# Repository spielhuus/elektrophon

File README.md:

# **<font size="24">*elektrophon*</font>** 

**elektrophon** is a collection of modular synthesizer modules i have built. The module folders contain the schema and PCB files for kicad. You can find all the required files for changing the schemas and building gerber files in the projects.  

## **<font size="24">*ressources*</font>** 

ressources on the internet which provide information about electronic instruments.

* [Thomas Henry](http://birthofasynth.com/Thomas_Henry/TH_main.html) modules archived by [Scott Stites](http://birthofasynth.com/index.html). 
  * The [Electronic Music Circuits: The Reprints](https://web.archive.org/web/20190907204304/https://static.miraheze.org/sdiywiki/5/5d/The_Reprint_Collection_by_Thomas_Henry_CC_BY_NC.pdf) from Thomas Henry.
* [Synthesizer DIY pages of René Schmitz](https://www.schmitzbits.de/index.html)
* [Music from outer space](http://musicfromouterspace.com/)
* [yusynth: modular synth project](http://www.yusynth.net/Modular/index_en.html)
* [Ken Stones - CGS (Cat Girl Synth)](http://www.elby-designs.com/webtek/cgs/cgs.htm)
* [Osamu Hoshuyama - Unusual Synthesizer Circuits)](http://www5b.biglobe.ne.jp/~houshu/synth/)
* pdf collection of the [polyphony](http://www.muzines.co.uk/mags/pl/all) magazine
* free [electronotes](http://electronotes.netfirms.com/free.htm) newsletter published by Bernie Hutchins.

## **<font size="24">*featured software*</font>** 

list of some third party software used to develop the modules. for a complete list go to the arbeitsplatz article.

* [KiCad EDA](https://kicad.org/) A Cross Platform and Open Source Electronics Design Automation Suite.
* [ngspice](http://ngspice.sourceforge.net/index.html) is an open source spice simulator for electric and electronic circuits.
* [PySpice](https://pyspice.fabrice-salvaire.fr/releases/v1.4/overview.html) is an open source Python module which provides a Python interface to the Ngspice and Xyce circuit simulators.
* [Jupyter](https://jupyter.org/) interactive Python notebook.  
* [SchemDraw](https://schemdraw.readthedocs.io/en/latest/index.html)  is a Python package for producing electrical circuit schematic diagrams.

---

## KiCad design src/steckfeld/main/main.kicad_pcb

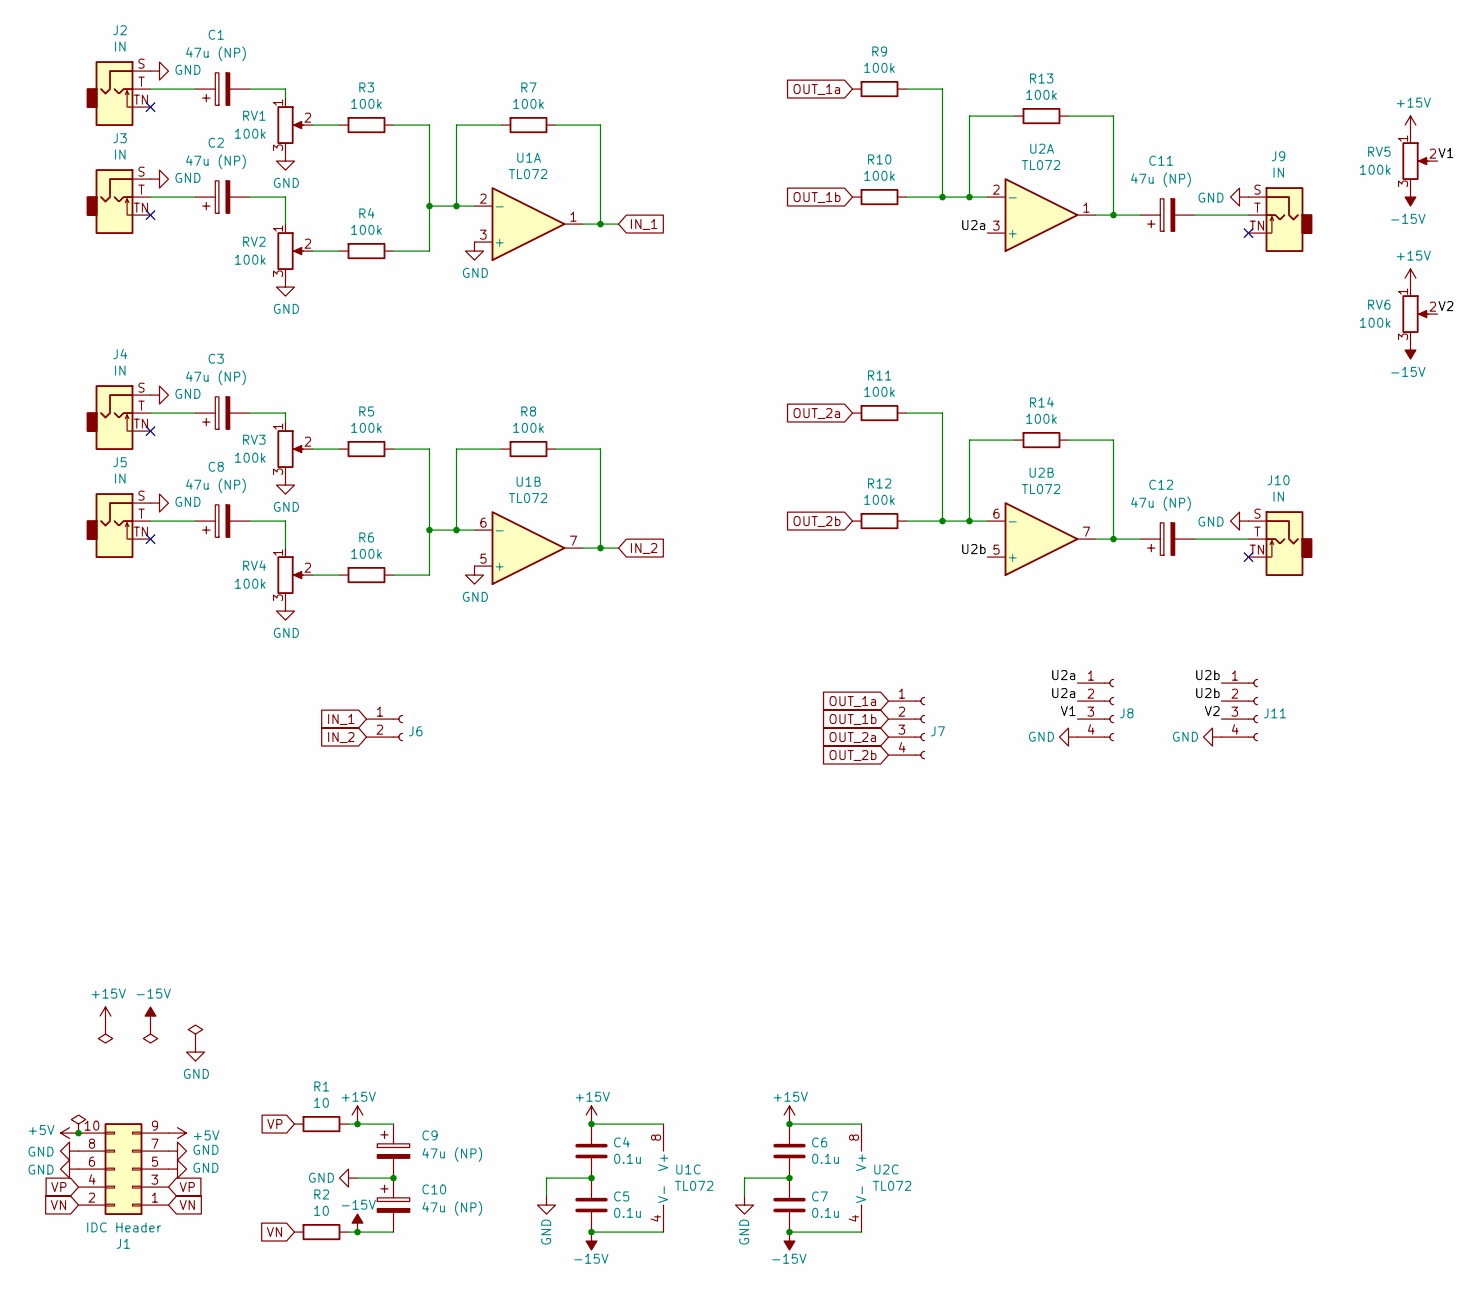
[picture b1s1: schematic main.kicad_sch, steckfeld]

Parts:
C1, C2, C3, C8, C11, C12: 47u (NP); PinSocket_1x02_P2.54mm_Vertical
C4, C5, C6, C7: 0.1u; C_Disc_D3.4mm_W2.1mm_P2.50mm
C9, C10: 47u (NP); CP_Radial_D5.0mm_P2.00mm
J1: IDC Header; IDC-Header_2x05_P2.54mm_Vertical
J2, J3, J4, J5, J9, J10: IN; Jack_3.5mm_WQP-PJ398SM_Vertical
J6: Conn_01x02_Female; PinSocket_1x02_P2.54mm_Vertical
J7, J8, J11: Conn_01x04_Female; PinSocket_1x04_P2.54mm_Vertical
R1, R2: 10; R_Axial_DIN0204_L3.6mm_D1.6mm_P2.54mm_Vertical
R3, R4, R5, R6, R7, R8, R9, R10, R11, R12, R13, R14: 100k; PinSocket_1x02_P2.54mm_Vertical
RV1, RV2, RV3, RV4, RV5, RV6: 100k; Potentiometer_Bourns_PTV09A-1_Single_Vertical
U1, U2: TL072; DIP-8_W7.62mm_Socket

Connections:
+5V: J1.9, J1.10
+15V: C4.1, C6.1, C9.1, R1.1, RV5.1, RV6.1, U1.8 (V+), U2.8 (V+)
-15V: C5.2, C7.2, C10.2, R2.1, RV5.3, RV6.3, U1.4 (V-), U2.4 (V-)
/U2a: J8.1, J8.2, U2.3 (+)
/U2b: J11.1, J11.2, U2.5 (+)
/V1: J8.3, RV5.2
/V2: J11.3, RV6.2
GND: C4.2, C5.1, C6.2, C7.1, C9.2, C10.1, J1.5, J1.6, J1.7, J1.8, J2.S, J3.S, J4.S, J5.S, J8.4, J9.S, J10.S, J11.4, RV1.3, RV2.3, RV3.3, RV4.3, U1.3 (+), U1.5 (+)
IN_1: J6.1, R7.1, U1.1
IN_2: J6.2, R8.1, U1.7
unnamed: C1.1, J2.T
unnamed: C1.2, RV1.1
unnamed: C2.1, J3.T
unnamed: C2.2, RV2.1
unnamed: C3.1, J4.T
unnamed: C3.2, RV3.1
unnamed: C8.1, J5.T
unnamed: C8.2, RV4.1
unnamed: C11.1, R13.1, U2.1
unnamed: C11.2, J9.T
unnamed: C12.1, R14.1, U2.7
unnamed: C12.2, J10.T
unnamed: R3.1, R4.1, R7.2, U1.2 (-)
unnamed: R3.2, RV1.2
unnamed: R4.2, RV2.2
unnamed: R5.1, R6.1, R8.2, U1.6 (-)
unnamed: R5.2, RV3.2
unnamed: R6.2, RV4.2
unnamed: R9.1, R10.1, R13.2, U2.2 (-)
unnamed: R11.1, R12.1, R14.2, U2.6 (-)
OUT_1a: J7.1, R9.2
OUT_1b: J7.2, R10.2
OUT_2a: J7.3, R11.2
OUT_2b: J7.4, R12.2
VN: J1.1, J1.2, R2.2
VP: J1.3, J1.4, R1.2

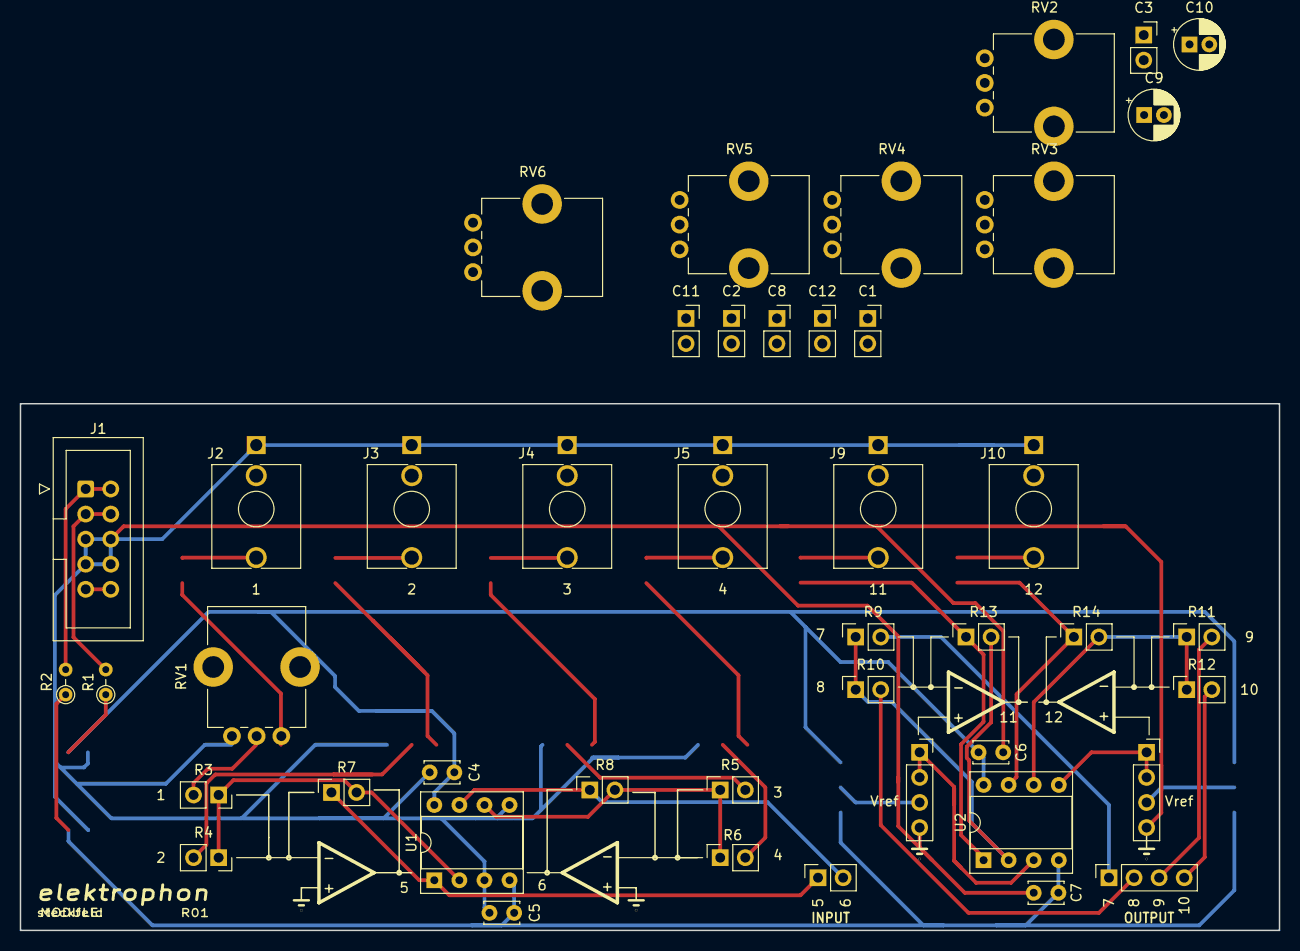
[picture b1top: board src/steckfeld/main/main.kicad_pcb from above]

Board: 2 copper layers, 127.5 x 53.3 mm, 45 parts (0 on the bottom side), 36 nets.

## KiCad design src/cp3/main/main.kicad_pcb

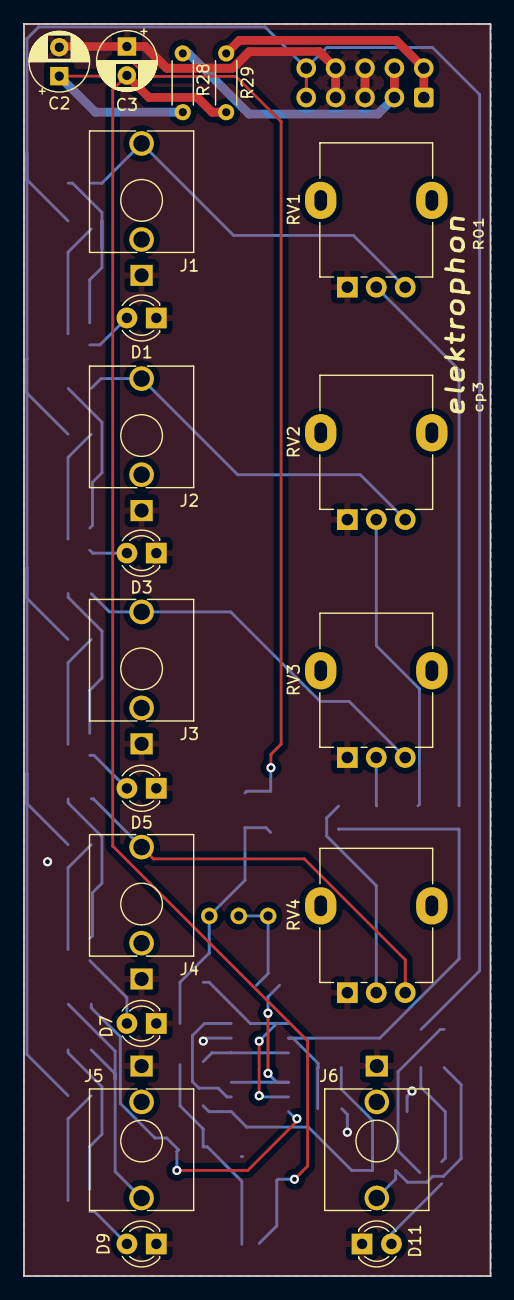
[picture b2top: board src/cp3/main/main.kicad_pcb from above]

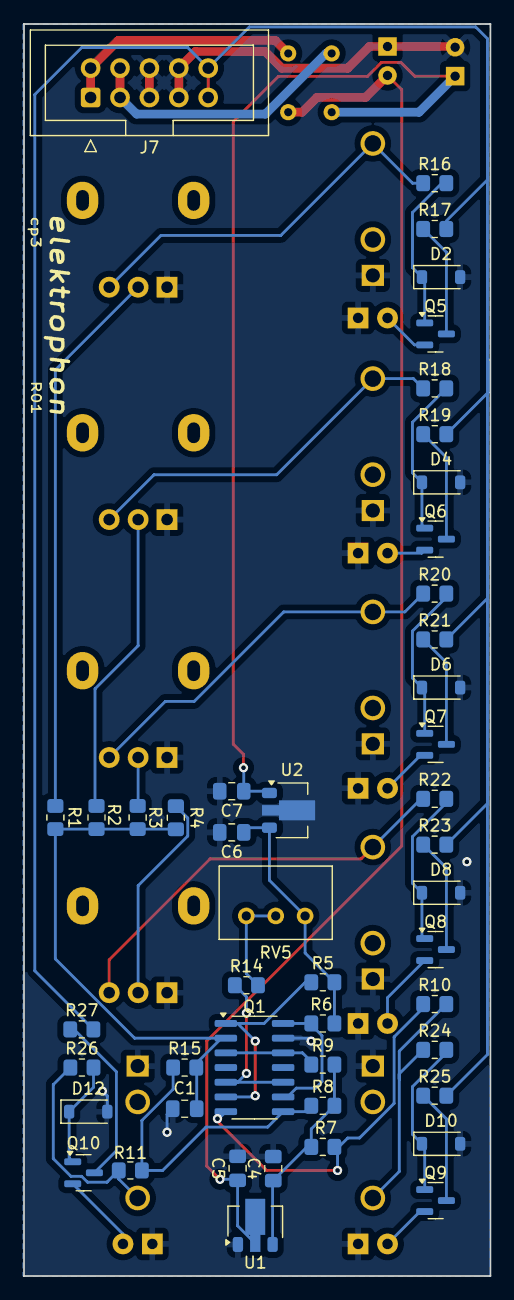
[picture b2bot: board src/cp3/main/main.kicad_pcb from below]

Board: 2 copper layers, 40.3 x 108.2 mm, 67 parts (47 on the bottom side), 44 nets.

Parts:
C1: 3.3n; C_0805_2012Metric_Pad1.18x1.45mm_HandSolder
C2, C3: 10u; CP_Radial_D5.0mm_P2.50mm
C4, C6: 0.33u; C_0805_2012Metric_Pad1.18x1.45mm_HandSolder
C5: 1.0u; C_0805_2012Metric_Pad1.18x1.45mm_HandSolder
C7: 0.01; C_0805_2012Metric_Pad1.18x1.45mm_HandSolder
D1, D3, D5, D7: LED (Green); LED_D3.0mm
D2, D4, D6, D8, D10, D12: 1N4148W; D_SOD-123
D9, D11: LED (Red); LED_D3.0mm
J1, J2, J3, J4, J5, J6: PJ398SM; Jack_3.5mm_WQP-PJ398SM_Vertical
J7: IDC_Header; IDC-Header_2x05_P2.54mm_Vertical
Q1: THAT340; SOIC-14_3.9x8.7mm_P1.27mm
Q5, Q6, Q7, Q8, Q9, Q10: MMBT3904; SOT-23
R1, R2, R3, R4: 22k; R_0805_2012Metric_Pad1.20x1.40mm_HandSolder
R5, R6: 15k; R_0805_2012Metric_Pad1.20x1.40mm_HandSolder
R7, R8: 560; R_0805_2012Metric_Pad1.20x1.40mm_HandSolder
R9: 6.8k; R_0805_2012Metric_Pad1.20x1.40mm_HandSolder
R10, R11: 100; R_0805_2012Metric_Pad1.20x1.40mm_HandSolder
R14: 200; R_0805_2012Metric_Pad1.20x1.40mm_HandSolder
R15: 47k; R_0805_2012Metric_Pad1.20x1.40mm_HandSolder
R16, R18, R20, R22, R24, R26: 100k; R_0805_2012Metric_Pad1.20x1.40mm_HandSolder
R17, R19, R21, R23, R25, R27: 5.1k; R_0805_2012Metric_Pad1.20x1.40mm_HandSolder
R28, R29: 10; R_Axial_DIN0204_L3.6mm_D1.6mm_P5.08mm_Horizontal
RV1, RV2, RV3, RV4: 50k (A); Potentiometer_Alpha_RD901F-40-00D_Single_Vertical
RV5: 100; Potentiometer_Bourns_3299W_Vertical
U1: NJM79L06; SOT-89-3
U2: uA7812; SOT-89-3

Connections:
+5V: J7.9, J7.10, R17.2, R19.2, R21.2, R23.2, R25.2, R27.2
+12V: C6.1, R5.2, R6.1, RV5.3, U2.3 (OUT)
+15V: C2.1, C7.1, R28.2, U2.1 (IN)
-6V: C4.1, R7.2, R8.2, R9.2, U1.3 (VO)
-15V: C3.2, C5.1, R29.1, U1.2 (VI)
/IN_1: R1.1, RV1.2
/IN_2: R2.2, RV2.2
/IN_3: R3.2, RV3.2
/IN_4: R4.2, RV4.2
/IN_a: J1.T, R16.1, RV1.3
/IN_b: J2.T, R18.1, RV2.3
/IN_c: J3.T, R20.1, RV3.3
/IN_d: J4.T, R22.1, RV4.3
/OUT_A: J5.T, R10.2, R24.1
/OUT_B: J6.T, R11.2, R26.1
/VN: J7.1, J7.2, R29.2
/VP: J7.3, J7.4, R28.1
GND: C1.2, C2.2, C3.1, C4.2, C5.2, C6.2, C7.2, D1.1 (K), D2.2 (A), D3.1 (K), D4.2 (A), D5.1 (K), D6.2 (A), D7.1 (K), D8.2 (A), D9.1 (K), D10.2 (A), D11.1 (K), D12.2 (A), J1.S, J2.S, J3.S, J4.S, J5.S, J6.S, J7.5, J7.6, J7.7, J7.8, Q1.13 (B), RV1.1, RV2.1, RV3.1, RV4.1, U1.1 (GND), U2.2 (GND)
unnamed: D1.2 (A), Q5.2 (E)
unnamed: D2.1 (K), Q5.1 (B), R16.2
unnamed: D3.2 (A), Q6.2 (E)
unnamed: D4.1 (K), Q6.1 (B), R18.2
unnamed: D5.2 (A), Q7.2 (E)
unnamed: D6.1 (K), Q7.1 (B), R20.2
unnamed: D7.2 (A), Q8.2 (E)
unnamed: D8.1 (K), Q8.1 (B), R22.2
unnamed: D9.2 (A), Q9.2 (E)
unnamed: D10.1 (K), Q9.1 (B), R24.2
unnamed: D11.2 (A), Q10.2 (E)
unnamed: D12.1 (K), Q10.1 (B), R26.2
unnamed: C1.1, Q1.2 (B), R1.2, R2.1, R3.1, R4.1, R15.2
unnamed: Q1.1 (C), Q1.6 (B), R5.1
unnamed: Q1.3 (E), Q1.12 (E), R9.1
unnamed: Q1.9 (B), Q1.14 (C), R6.2
unnamed: Q1.5 (C), Q1.10, R14.1
unnamed: Q1.7 (E), R7.1, R10.1
unnamed: Q1.8 (E), R8.1, R11.1, R15.1
unnamed: Q5.3 (C), R17.1
unnamed: Q6.3 (C), R19.1
unnamed: Q7.3 (C), R21.1
unnamed: Q8.3 (C), R23.1
unnamed: Q9.3 (C), R25.1
unnamed: Q10.3 (C), R27.1
unnamed: R14.2, RV5.1, RV5.2

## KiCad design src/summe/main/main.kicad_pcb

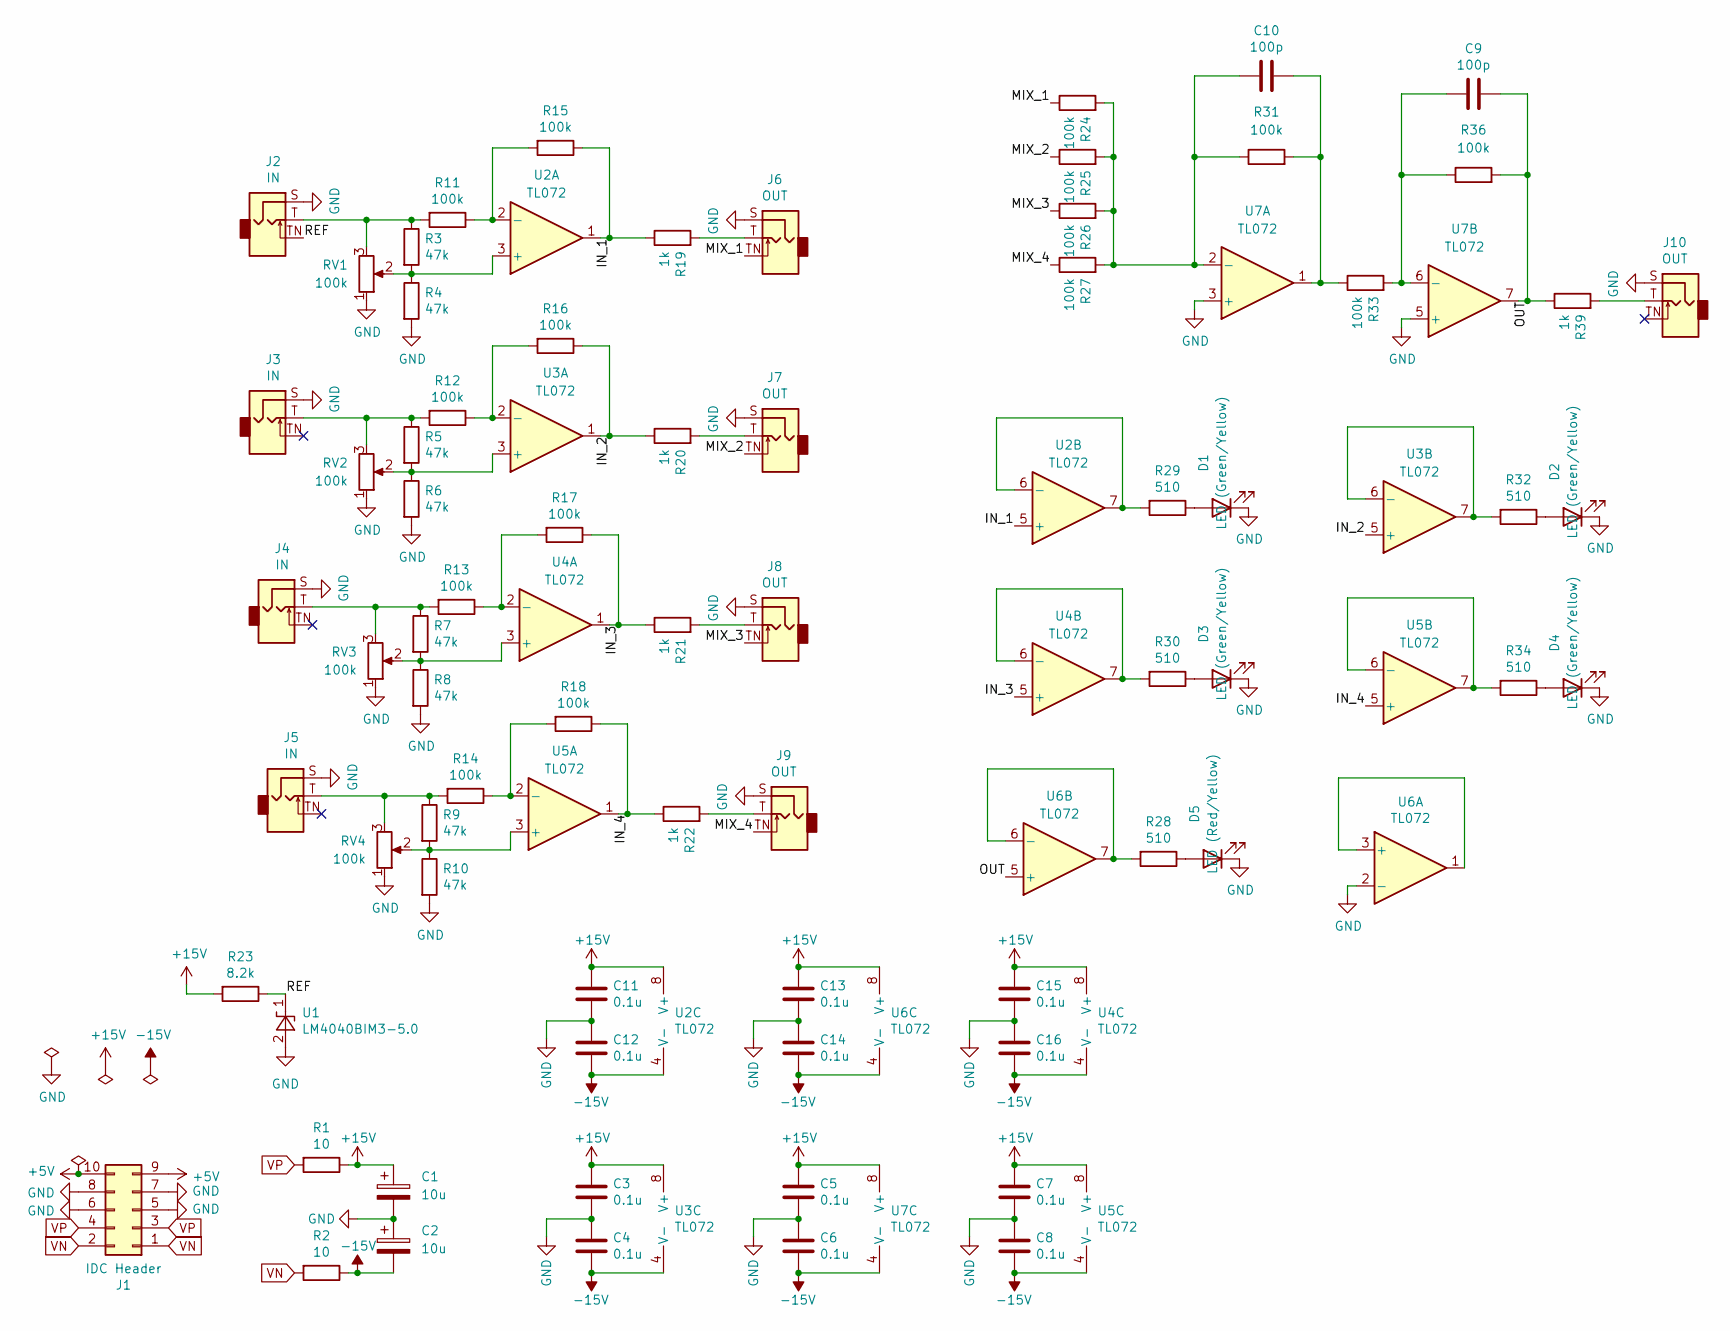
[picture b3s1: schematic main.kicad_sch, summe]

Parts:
C1, C2: 10u; CP_Radial_D5.0mm_P2.50mm
C3, C4, C5, C6, C7, C8, C11, C12, C13, C14, C15, C16: 0.1u; C_0805_2012Metric_Pad1.18x1.45mm_HandSolder
C9, C10: 100p; C_0805_2012Metric_Pad1.18x1.45mm_HandSolder
D1, D2, D3, D4: LED (Green/Yellow); LED_D3.0mm
D5: LED (Red/Yellow); LED_D3.0mm
J1: IDC Header; IDC-Header_2x05_P2.54mm_Vertical
J2, J3, J4, J5: IN; Jack_3.5mm_WQP-PJ398SM_Vertical
J6, J7, J8, J9, J10: OUT; Jack_3.5mm_WQP-PJ398SM_Vertical
R1, R2: 10; R_Axial_DIN0204_L3.6mm_D1.6mm_P2.54mm_Vertical
R3, R4, R5, R6, R7, R8, R9, R10: 47k; R_0805_2012Metric_Pad1.20x1.40mm_HandSolder
R11, R12, R13, R14, R15, R16, R17, R18, R24, R25, R26, R27, R31, R33, R36: 100k; R_0805_2012Metric_Pad1.20x1.40mm_HandSolder
R19, R20, R21, R22, R39: 1k; R_0805_2012Metric_Pad1.20x1.40mm_HandSolder
R23: 8.2k; R_0805_2012Metric_Pad1.20x1.40mm_HandSolder
R28, R29, R30, R32, R34: 510; R_0805_2012Metric_Pad1.20x1.40mm_HandSolder
RV1, RV2, RV3, RV4: 100k; Potentiometer_Alpha_RD901F-40-00D_Single_Vertical
U1: LM4040BIM3-5.0; SOT-23
U2, U3, U4, U5, U6, U7: TL072; SOIC-8_3.9x4.9mm_P1.27mm

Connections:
+5V: J1.9, J1.10
+15V: C1.1, C3.1, C5.1, C7.1, C11.1, C13.1, C15.1, R1.1, R23.2, U2.8 (V+), U3.8 (V+), U4.8 (V+), U5.8 (V+), U6.8 (V+), U7.8 (V+)
-15V: C2.2, C4.2, C6.2, C8.2, C12.2, C14.2, C16.2, R2.1, U2.4 (V-), U3.4 (V-), U4.4 (V-), U5.4 (V-), U6.4 (V-), U7.4 (V-)
/IN_1: R15.1, R19.1, U2.1, U2.5 (+)
/IN_2: R16.1, R20.1, U3.1, U3.5 (+)
/IN_3: R17.1, R21.1, U4.1, U4.5 (+)
/IN_4: R18.1, R22.1, U5.1, U5.5 (+)
/MIX_1: J6.TN, R24.1
/MIX_2: J7.TN, R25.1
/MIX_3: J8.TN, R26.1
/MIX_4: J9.TN, R27.1
/OUT: C9.1, R36.2, R39.1, U6.5 (+), U7.7
/REF: J2.TN, R23.1, U1.1 (K)
GND: C1.2, C2.1, C3.2, C4.1, C5.2, C6.1, C7.2, C8.1, C11.2, C12.1, C13.2, C14.1, C15.2, C16.1, D1.1 (K), D2.1 (K), D3.1 (K), D4.1 (K), D5.1 (K), J1.5, J1.6, J1.7, J1.8, J2.S, J3.S, J4.S, J5.S, J6.S, J7.S, J8.S, J9.S, J10.S, R4.2, R6.2, R8.2, R10.2, RV1.1, RV2.1, RV3.1, RV4.1, U1.2 (A), U6.2 (-), U7.3 (+), U7.5 (+)
unnamed: C10.1, R31.2, R33.1, U7.1
unnamed: D1.2 (A), R29.1
unnamed: D2.2 (A), R32.1
unnamed: D3.2 (A), R30.1
unnamed: D4.2 (A), R34.1
unnamed: D5.2 (A), R28.1
unnamed: J2.T, R3.1, R11.2, RV1.3
unnamed: J3.T, R5.1, R12.2, RV2.3
unnamed: J4.T, R7.1, R13.2, RV3.3
unnamed: J5.T, R9.1, R14.2, RV4.3
unnamed: J6.T, R19.2
unnamed: J7.T, R20.2
unnamed: J8.T, R21.2
unnamed: J9.T, R22.2
unnamed: J10.T, R39.2
unnamed: R3.2, R4.1, RV1.2, U2.3 (+)
unnamed: R11.1, R15.2, U2.2 (-)
unnamed: R29.2, U2.6 (-), U2.7
unnamed: R5.2, R6.1, RV2.2, U3.3 (+)
unnamed: R12.1, R16.2, U3.2 (-)
unnamed: R32.2, U3.6 (-), U3.7
unnamed: R7.2, R8.1, RV3.2, U4.3 (+)
unnamed: R13.1, R17.2, U4.2 (-)
unnamed: R30.2, U4.6 (-), U4.7
unnamed: R9.2, R10.1, RV4.2, U5.3 (+)
unnamed: R14.1, R18.2, U5.2 (-)
unnamed: R34.2, U5.6 (-), U5.7
unnamed: U6.1, U6.3 (+)
unnamed: R28.2, U6.6 (-), U6.7
unnamed: C10.2, R24.2, R25.2, R26.2, R27.2, R31.1, U7.2 (-)
unnamed: C9.2, R33.2, R36.1, U7.6 (-)
VN: J1.1, J1.2, R2.2
VP: J1.3, J1.4, R1.2

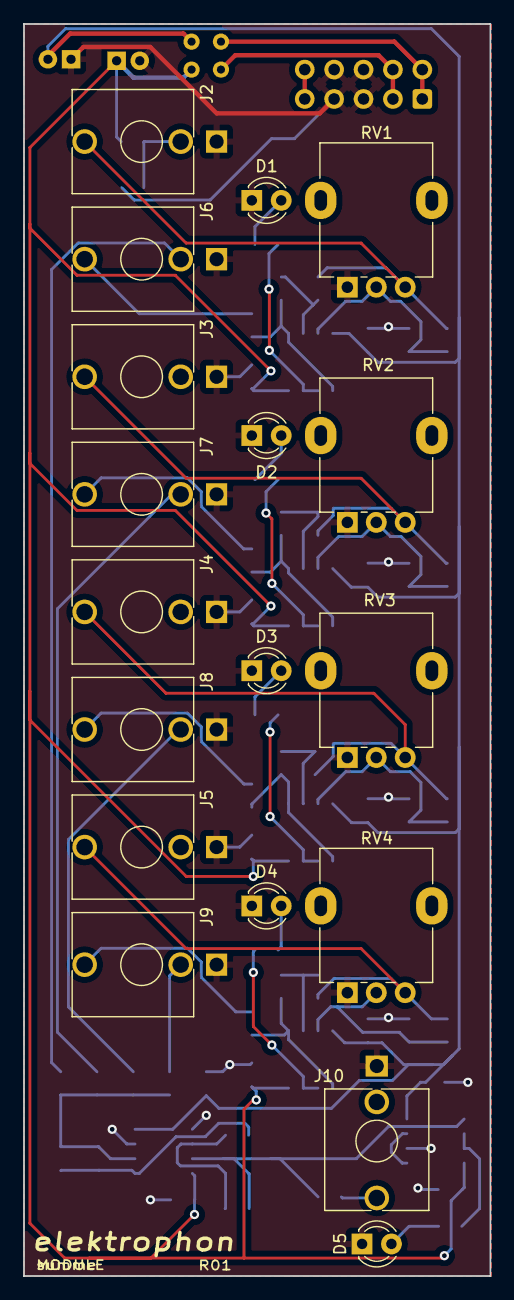
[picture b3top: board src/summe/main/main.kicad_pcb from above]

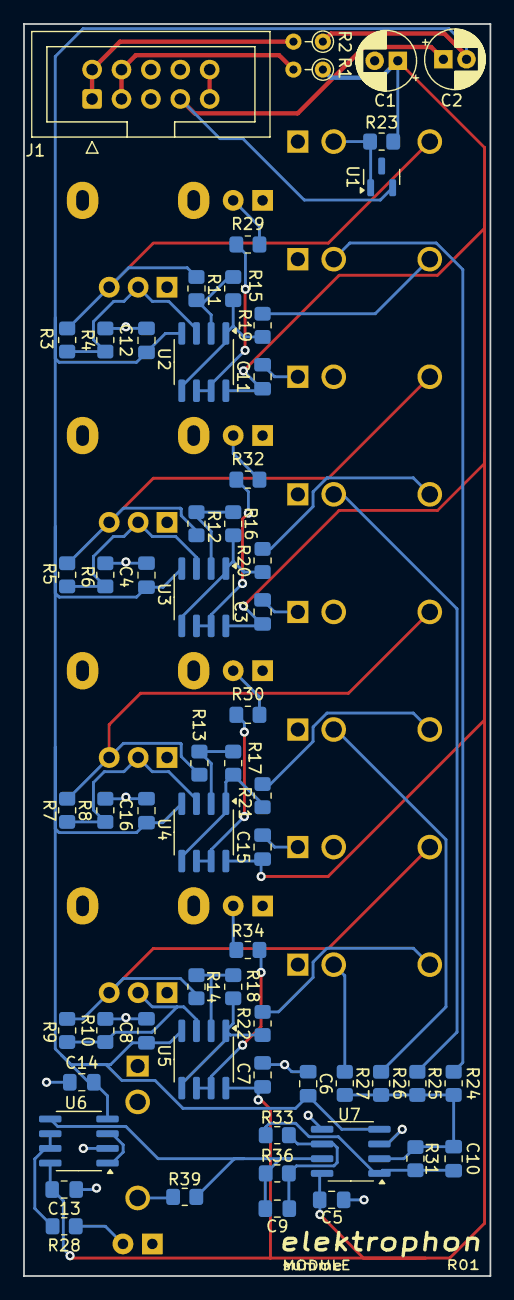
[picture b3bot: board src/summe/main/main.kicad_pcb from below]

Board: 2 copper layers, 40.3 x 108.2 mm, 78 parts (60 on the bottom side), 47 nets.

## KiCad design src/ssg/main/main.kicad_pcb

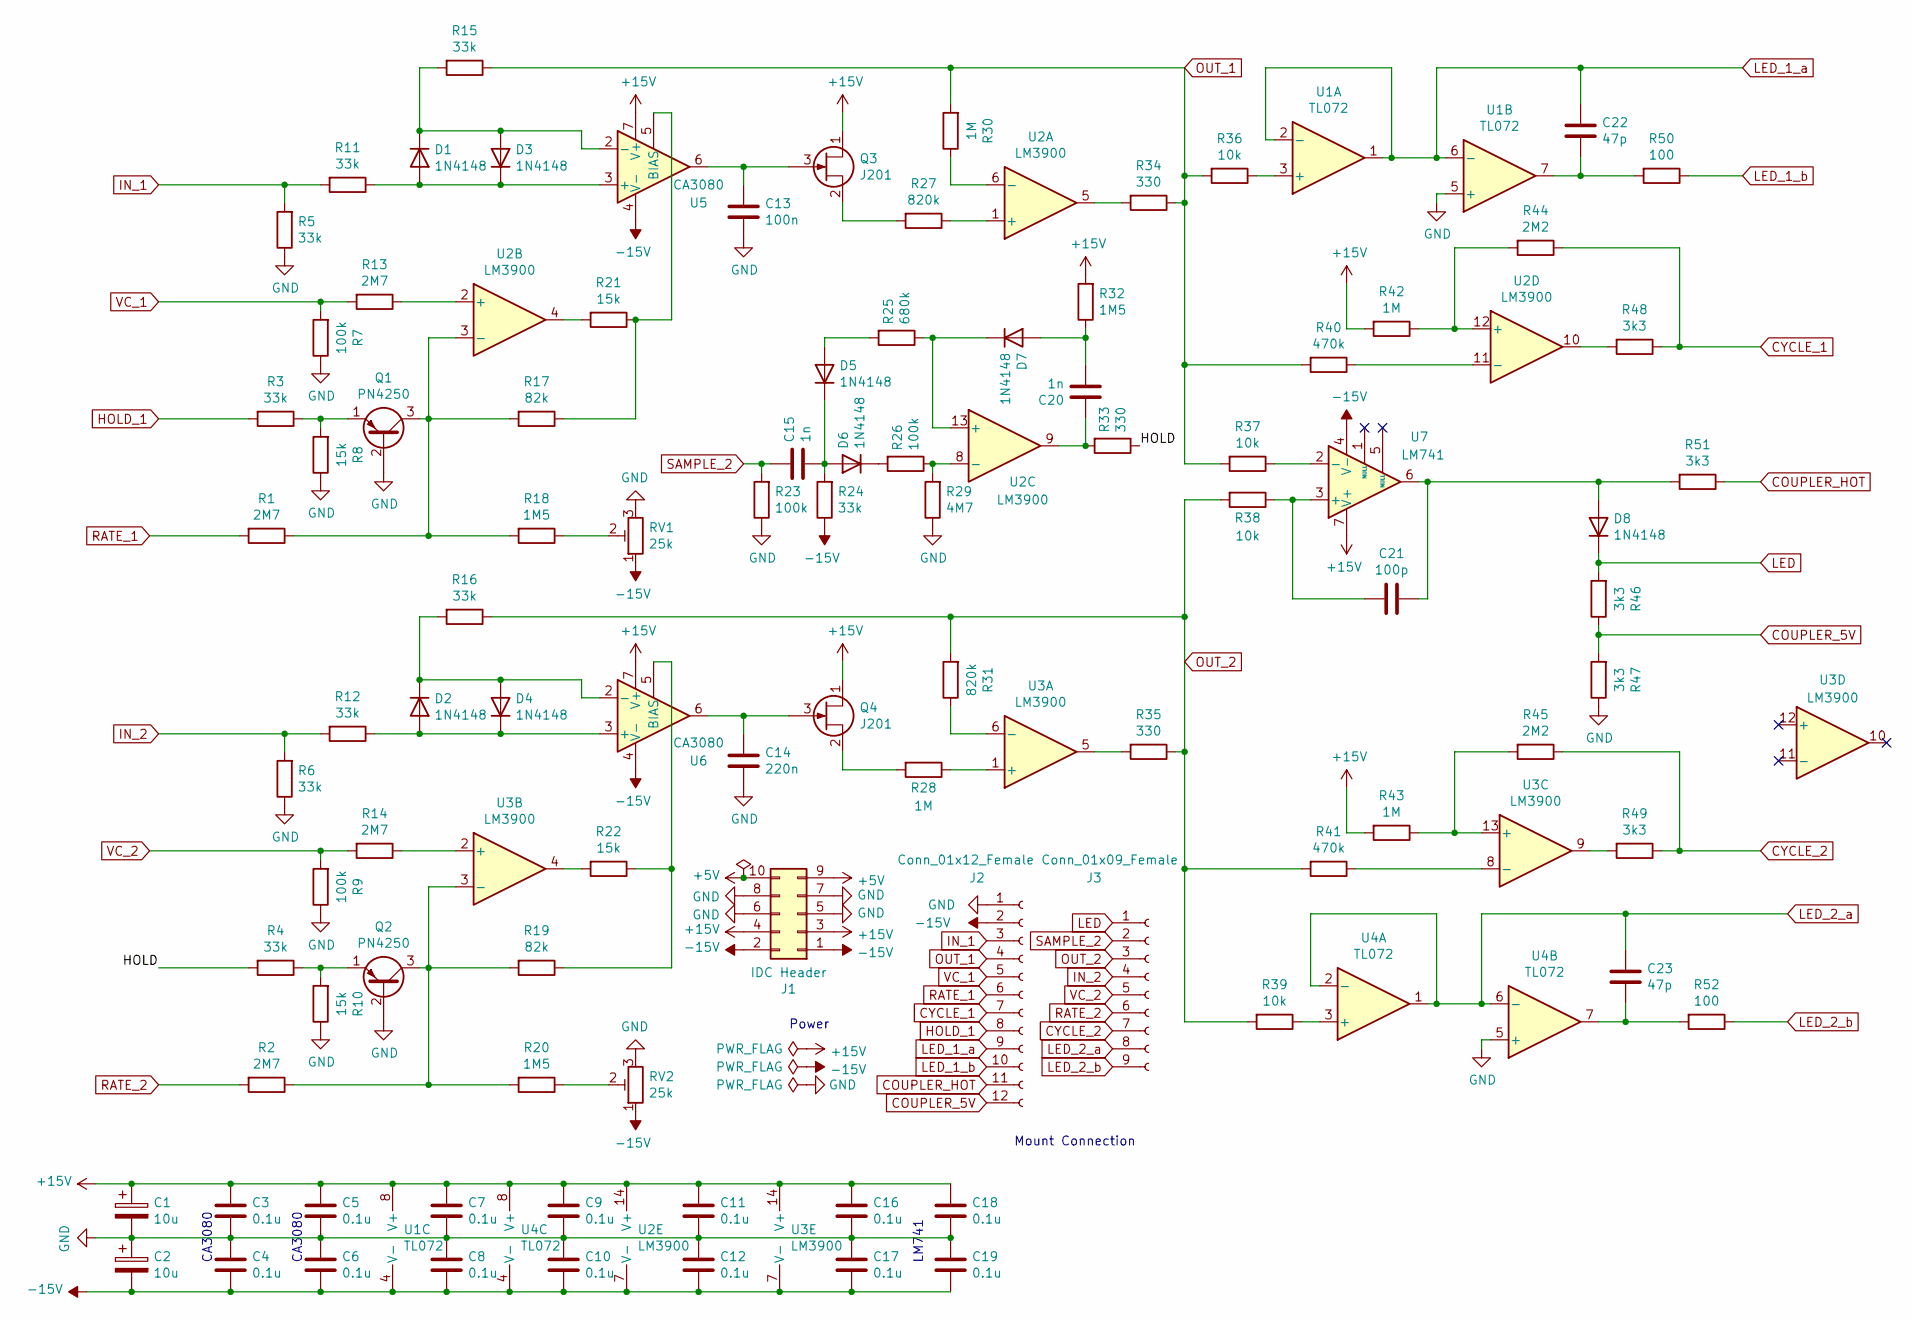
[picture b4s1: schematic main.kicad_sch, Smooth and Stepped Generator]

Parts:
C1, C2: 10u; CP_Radial_D5.0mm_P2.50mm
C3, C4, C5, C6, C7, C8, C9, C10, C11, C12, C16, C17, C18, C19: 0.1u; C_Disc_D3.4mm_W2.1mm_P2.50mm
C13: 100n; C_Disc_D3.4mm_W2.1mm_P2.50mm
C14: 220n; C_Disc_D4.3mm_W1.9mm_P5.00mm
C15, C20: 1n; C_Disc_D3.4mm_W2.1mm_P2.50mm
C21: 100p; C_Disc_D3.4mm_W2.1mm_P2.50mm
C22, C23: 47p; C_Disc_D3.4mm_W2.1mm_P2.50mm
D1, D2, D3, D4, D5, D6, D7, D8: 1N4148; D_DO-35_SOD27_P7.62mm_Horizontal
J1: IDC Header; IDC-Header_2x05_P2.54mm_Vertical
J2: Conn_01x12_Female; PinSocket_1x12_P2.54mm_Vertical
J3: Conn_01x09_Female; PinSocket_1x09_P2.54mm_Vertical
Q1, Q2: PN4250; TO-92_Inline
Q3, Q4: J201; TO-92_Inline
R1, R2, R13, R14: 2M7; R_Axial_DIN0207_L6.3mm_D2.5mm_P10.16mm_Horizontal
R3, R4, R5, R6, R11, R12, R15, R16, R24: 33k; R_Axial_DIN0207_L6.3mm_D2.5mm_P10.16mm_Horizontal
R7, R9, R23, R26: 100k; R_Axial_DIN0207_L6.3mm_D2.5mm_P10.16mm_Horizontal
R8, R10, R21, R22: 15k; R_Axial_DIN0207_L6.3mm_D2.5mm_P10.16mm_Horizontal
R17, R19: 82k; R_Axial_DIN0207_L6.3mm_D2.5mm_P10.16mm_Horizontal
R18, R20, R32: 1M5; R_Axial_DIN0207_L6.3mm_D2.5mm_P10.16mm_Horizontal
R25: 680k; R_Axial_DIN0207_L6.3mm_D2.5mm_P10.16mm_Horizontal
R27, R31: 820k; R_Axial_DIN0207_L6.3mm_D2.5mm_P10.16mm_Horizontal
R28, R30, R42, R43: 1M; R_Axial_DIN0207_L6.3mm_D2.5mm_P10.16mm_Horizontal
R29: 4M7; R_Axial_DIN0207_L6.3mm_D2.5mm_P10.16mm_Horizontal
R33, R34, R35: 330; R_Axial_DIN0207_L6.3mm_D2.5mm_P10.16mm_Horizontal
R36, R37, R38, R39: 10k; R_Axial_DIN0207_L6.3mm_D2.5mm_P10.16mm_Horizontal
R40, R41: 470k; R_Axial_DIN0207_L6.3mm_D2.5mm_P10.16mm_Horizontal
R44, R45: 2M2; R_Axial_DIN0207_L6.3mm_D2.5mm_P10.16mm_Horizontal
R46, R47, R48, R49, R51: 3k3; R_Axial_DIN0207_L6.3mm_D2.5mm_P10.16mm_Horizontal
R50, R52: 100; R_Axial_DIN0207_L6.3mm_D2.5mm_P10.16mm_Horizontal
RV1, RV2: 25k; Potentiometer_Bourns_3296Z_Horizontal
U1, U4: TL072; DIP-8_W7.62mm_Socket
U2, U3: LM3900; DIP-14_W7.62mm_Socket
U5, U6: CA3080; DIP-8_W7.62mm_Socket
U7: LM741; DIP-8_W7.62mm_Socket

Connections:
+5V: J1.9, J1.10
+15V: C1.1, C3.1, C5.1, C7.1, C9.1, C11.1, C16.1, C18.1, J1.3, J1.4, Q3.1 (D), Q4.1 (D), R32.2, R42.2, R43.2, U1.8 (V+), U2.14 (V+), U3.14 (V+), U4.8 (V+), U5.7 (V+), U6.7 (V+), U7.7 (V+)
-15V: C2.2, C4.2, C6.2, C8.2, C10.2, C12.2, C17.2, C19.2, J1.1, J1.2, J2.2, R24.1, RV1.1, RV2.1, U1.4 (V-), U2.7 (V-), U3.7 (V-), U4.4 (V-), U5.4 (V-), U6.4 (V-), U7.4 (V-)
/HOLD: R4.2, R33.1
COUPLER_5V: J2.12, R46.1, R47.2
COUPLER_HOT: J2.11, R51.1
CYCLE_1: J2.7, R44.1, R48.1
CYCLE_2: J3.7, R45.1, R49.1
GND: C1.2, C2.1, C3.2, C4.1, C5.2, C6.1, C7.2, C8.1, C9.2, C10.1, C11.2, C12.1, C13.2, C14.2, C16.2, C17.1, C18.2, C19.1, J1.5, J1.6, J1.7, J1.8, J2.1, Q1.2 (B), Q2.2 (B), R5.1, R6.1, R7.1, R8.1, R9.1, R10.1, R23.1, R29.1, R47.1, RV1.3, RV2.3, U1.5 (+), U4.5 (+)
HOLD_1: J2.8, R3.2
IN_1: J2.3, R5.2, R11.2
IN_2: J3.4, R6.2, R12.2
LED: D8.1 (K), J3.1, R46.2
LED_1_a: C22.1, J2.9, U1.1, U1.2 (-), U1.6 (-)
LED_1_b: J2.10, R50.1
LED_2_a: C23.1, J3.8, U4.1, U4.2 (-), U4.6 (-)
LED_2_b: J3.9, R52.1
unnamed: C20.1, R33.2, U2.9
unnamed: C22.2, R50.2, U1.7
unnamed: C23.2, R52.2, U4.7
unnamed: D1.2 (A), D3.1 (K), R11.1, U5.3 (+)
unnamed: D1.1 (K), D3.2 (A), R15.2, U5.2 (-)
unnamed: D2.2 (A), D4.1 (K), R12.1, U6.3 (+)
unnamed: D2.1 (K), D4.2 (A), R16.2, U6.2 (-)
unnamed: D5.2 (A), R25.2
unnamed: C15.2, D5.1 (K), D6.2 (A), R24.2
unnamed: D6.1 (K), R26.2
unnamed: C20.2, D7.2 (A), R32.1
unnamed: D7.1 (K), R25.1, U2.13 (+)
unnamed: C21.1, D8.2 (A), R51.2, U7.6
unnamed: Q1.3 (C), R1.1, R17.2, R18.2, U2.3 (-)
unnamed: Q1.1 (E), R3.1, R8.2
unnamed: Q2.3 (C), R2.1, R19.2, R20.2, U3.3 (-)
unnamed: Q2.1 (E), R4.1, R10.2
unnamed: C13.1, Q3.3 (G), U5.6
unnamed: Q3.2 (S), R27.2
unnamed: C14.1, Q4.3 (G), U6.6
unnamed: Q4.2 (S), R28.2
unnamed: R18.1, RV1.2
unnamed: R20.1, RV2.2
unnamed: R21.2, U2.4
unnamed: R22.2, U3.4
unnamed: R34.2, U2.5
unnamed: R35.2, U3.5
unnamed: R48.2, U2.10
unnamed: R49.2, U3.9
unnamed: R36.1, U1.3 (+)
unnamed: R27.1, U2.1 (+)
unnamed: R30.1, U2.6 (-)
unnamed: R13.1, U2.2 (+)
unnamed: R26.1, R29.2, U2.8 (-)
unnamed: R42.1, R44.2, U2.12 (+)
unnamed: R40.1, U2.11 (-)
unnamed: R28.1, U3.1 (+)
unnamed: R31.1, U3.6 (-)
unnamed: R14.1, U3.2 (+)
unnamed: R43.1, R45.2, U3.13 (+)
unnamed: R41.1, U3.8 (-)
unnamed: R39.1, U4.3 (+)
unnamed: R17.1, R21.1, U5.5 (BIAS)
unnamed: R19.1, R22.1, U6.5 (BIAS)
unnamed: C21.2, R38.1, U7.3 (+)
unnamed: R37.1, U7.2 (-)
OUT_1: J2.4, R15.1, R30.2, R34.1, R36.2, R37.2, R40.2
OUT_2: J3.3, R16.1, R31.2, R35.1, R38.2, R39.2, R41.2
RATE_1: J2.6, R1.2
RATE_2: J3.6, R2.2
SAMPLE_2: C15.1, J3.2, R23.2
VC_1: J2.5, R7.2, R13.2
VC_2: J3.5, R9.2, R14.2

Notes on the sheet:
CA3080
Power
LM741
Mount Connection

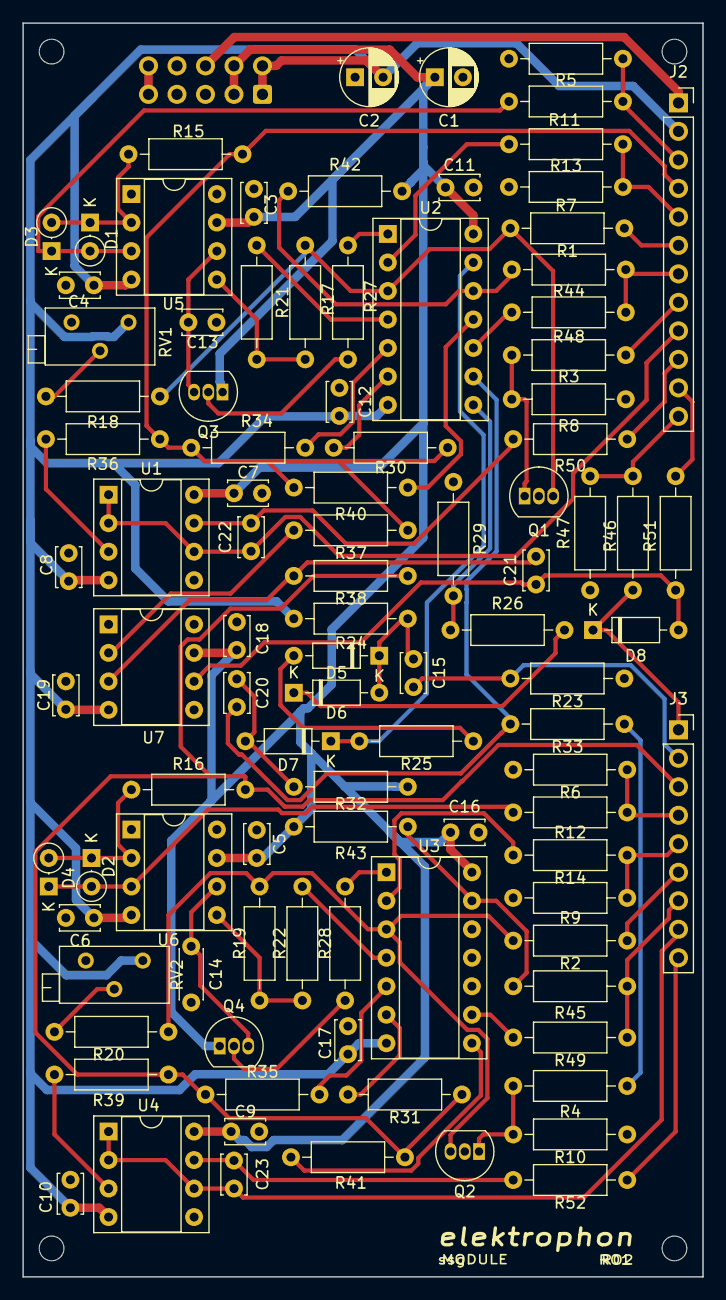
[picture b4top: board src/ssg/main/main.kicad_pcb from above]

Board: 2 copper layers, 60.6 x 111.8 mm, 99 parts (1 on the bottom side), 70 nets.

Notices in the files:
README.md:
CC BY-SA
src/basspp/main/main.kicad_pcb:
License CC BY 4.0 - Attribution 4.0 International
